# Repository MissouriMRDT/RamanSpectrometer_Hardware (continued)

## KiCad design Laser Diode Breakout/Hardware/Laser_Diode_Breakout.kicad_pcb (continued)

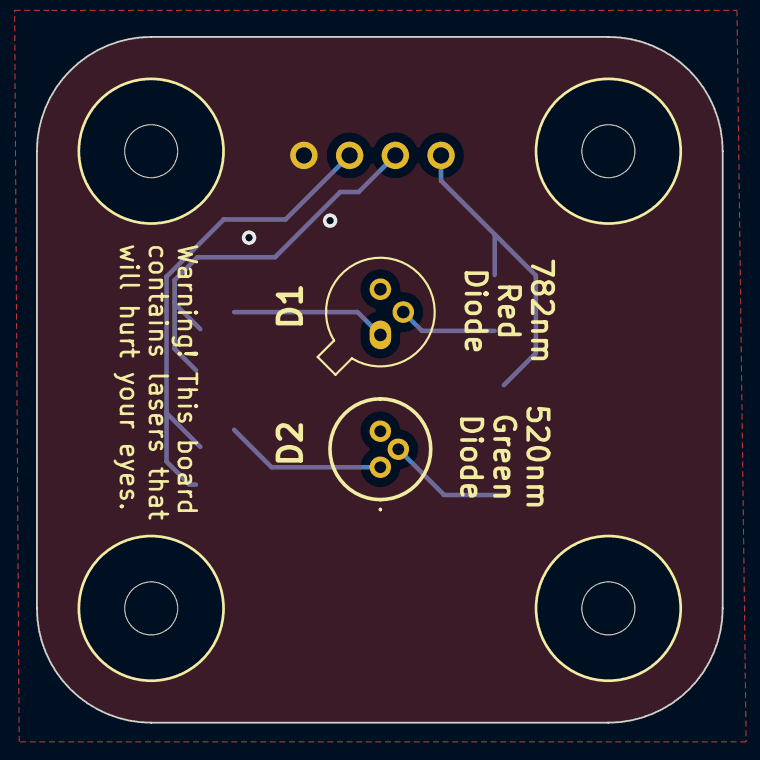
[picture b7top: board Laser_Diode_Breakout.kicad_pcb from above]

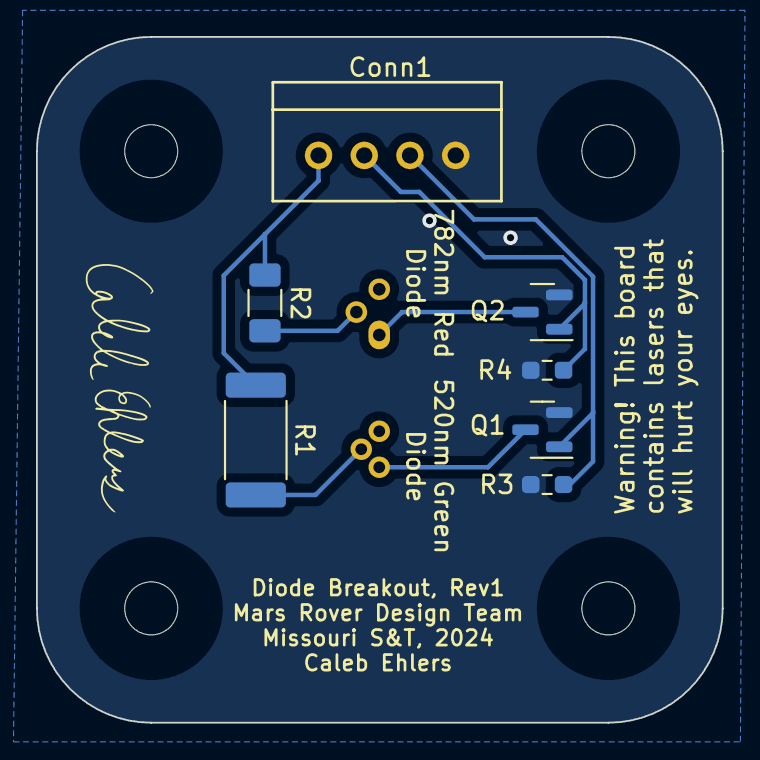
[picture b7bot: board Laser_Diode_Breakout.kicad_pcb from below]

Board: 2 copper layers, 38.1 x 38.1 mm, 13 parts (7 on the bottom side), 8 nets.

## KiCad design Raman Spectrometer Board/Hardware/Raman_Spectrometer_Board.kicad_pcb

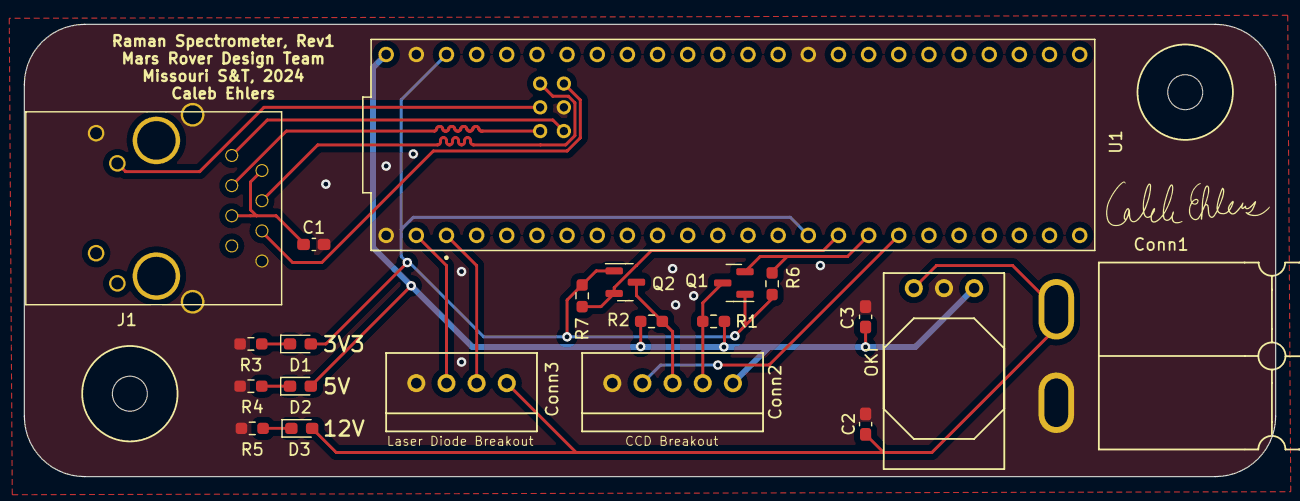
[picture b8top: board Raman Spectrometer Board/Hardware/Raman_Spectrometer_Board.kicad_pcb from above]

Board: 2 copper layers, 105.4 x 38.1 mm, 23 parts (0 on the bottom side), 20 nets.

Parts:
C1: 0.1µF; C_0603_1608Metric_Pad1.08x0.95mm_HandSolder
C2, C3: 10µF; C_0603_1608Metric_Pad1.08x0.95mm_HandSolder
Conn1: AndersonPP; Square_Anderson_2_H_Side_By_Side
Conn2: Molex_SL_05; MOLEX_SL_05_Vertical
Conn3: Molex_SL_04; MOLEX_SL_04_Vertical
D1, D2, D3: Green; LED_0603_1608Metric_Pad1.05x0.95mm_HandSolder
J1: RJ45_LED_Shielded; RJ45_Teensy
Q1, Q2: BSS138; SOT-23
R1, R2, R6, R7: 4.7k; R_0603_1608Metric_Pad0.98x0.95mm_HandSolder
R3: 100; R_0603_1608Metric_Pad0.98x0.95mm_HandSolder
R4: 300; R_0603_1608Metric_Pad0.98x0.95mm_HandSolder
R5: 1k; R_0603_1608Metric_Pad0.98x0.95mm_HandSolder
U1: Teensy4.1_DEV-16771; Teensy_4_1_Ethernet
U2: OKI; OKI_Horizontal
V1, V2: Via; 4_40_Hole

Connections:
+3V3: D1.2 (A), Q1.1 (G), Q2.1 (G), R6.1, R7.1, U1.3.3V_1 (3.3V), U1.3.3V_2 (3.3V)
+5V: C3.1, Conn2.1, D2.2 (A), R1.1, R2.1, U1.VIN, U2.3 (Vo)
+12V: C2.1, Conn1.2 (V+Log), Conn3.1, D3.2 (A), U2.1 (Vi)
CCD_CLK_3V3: Q1.2 (S), R6.2, U1.25 (A11)
CCD_CLK_5V: Conn2.2, Q1.3 (D), R1.2
CCD_ROG_3V3: Q2.2 (S), R7.2, U1.24 (A10)
CCD_ROG_5V: Conn2.3, Q2.3 (D), R2.2
CCD_Vout: Conn2.4, U1.26 (A12)
GND: C1.2, C2.2, C3.2, Conn1.1 (GND), Conn2.5, Conn3.4, J1.8, J1.9, J1.SH, R3.2, R4.2, R5.2, U1.GND1 (GND), U1.GND2 (GND), U1.GND3 (GND), U1.GND5 (GND), U2.2 (GND)
Green_LED: Conn3.3, U1.0 (RX1)
LED: J1.10, U1.LED
unnamed: C1.1, J1.2, J1.5
unnamed: D1.1 (K), R3.1
unnamed: D2.1 (K), R4.1
unnamed: D3.1 (K), R5.1
R+: J1.4, U1.R+
R-: J1.6, U1.R-
Red_LED: Conn3.2, U1.1 (TX1)
T+: J1.1, U1.T+
T-: J1.3, U1.T-

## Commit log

2023-09-09 chore: created CCD Breakout project
2023-09-09 chore: created empty schematics
2023-09-09 feat: add teensy and ethernet
2023-09-09 Adjust file structure
2023-09-11 feat: created ILX511 symbol for CCD Breakout
2023-09-12 //WIP CCD Breakout
2023-09-12 chore: delete duplicate Raman board files
2023-09-15 Finshed CCD breakout
2023-09-24 Made Laser Diode breakout
2023-09-24 added laser breakout to raman board
2023-09-24 finished adding boxes to ramen board
2023-09-24 generated BOM
2023-09-24 I forgot to save everything for the last commit
2023-09-24 fix: switched connectors to Molex
2023-09-25 fix: replaced net labels with text
2023-09-25 misc schematic review changes
2023-09-25 fix: use mosfets to control diodes
2023-09-25 chore: resized Raman Board
2023-09-28 changed AndersonPP to V+ Log
2023-10-02 feat: aligned components for Raman board
2023-10-02 //WIP
2023-10-03 feat: finish Raman board
2023-10-03 fix: changes from malacki
2023-10-13 //WIP working on fixing diodes
    we though one of the diodes required 2V, but that was its reverse voltage. It actually wants 5.9, so we need to change the diode board to account
2023-10-14 fixed resitor values on diode board
2023-10-14 set footprints for most of laser diode breakout
2023-10-14 diode board layout general shape
2023-10-14 finished adding footprints to laser diode breakout
2023-10-14 added footprints to ccd breakout
    added all capacitors
    the only footprint left is the ccd
2023-10-14 closed kicad tabs
2023-10-14 finish diode breakout
2023-10-15 fix: changed ilx511 symbol library path
2023-10-15 created ilx511 footprint
2023-10-15 closed out of kicad tabs
2023-10-15 //WIP start ccd layout
2023-10-15 finish ccd
2023-10-15 added ground plane to diode board
2023-10-15 switched raman board to using vertical molex
2023-10-15 fixed ground plane in diode breakout
2023-10-15 rearrange components on raman board
2023-10-15 added signatures to all boards
2023-10-15 cleaned file structure
2023-10-15 rewired raman board
2023-10-15 clean up 3V3 wires
2023-10-15 removed little random traces
2023-10-15 finished raman board changes
2023-10-15 added label to raman board
2023-10-16 finish diode breakout changes
2023-10-16 adjusted page sizes for all boards
2023-10-16 finish ccd board
2023-10-16 adjust silkscreen on diode board
2023-10-16 adjust silkscreen for raman board
2023-10-16 removed small random traces
2023-10-19 fixed board name silkscreens
2023-10-21 generated step files
2023-10-21 closed kicad
2023-10-21 add 4.7k resistor to mosfets and regenerate BOM
2023-10-21 changes for layout review #2
2023-10-31 generated GERBS
2023-10-31 fix differential pairs and center LEDs on diode board
2023-10-31 regenerate GERBS
2023-11-03 changes from layout review #3
2024-09-26 Reset branch
2024-10-03 Added Diode Control
2024-10-03 Restoring Changes
2024-10-03 fix
    fixed from 2024rev1 push
2024-10-04 Added CCD Breakout
2024-10-04 Mounting Holes / Formatting
2024-10-04 status
2024-10-04 Finished Raman Spectrometer Schematic. Merged Diode Breakout onto the board, but also left a connector in case we use a store-bought diode/external one off the board. Might want to check over the sch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
2024-10-04 Changed Labels
2024-10-05 Gantry and fan connector pins
2024-10-05 Started on BOM. Updated gantry and fan connectors
2024-10-06 Updated BOM a little bit
2024-10-10 Raman Schematic Review
    Made changes to the labels on the gantry connector and teensy.
2024-10-11 Added Mounting Holes
2024-10-11 CCD GND
2024-10-17 updated schematic
2024-10-17 Updated Bill of Materials
2024-10-17 updated BOM again
2024-10-24 footprints
2024-10-24 pcb layout
2024-10-25 PCB Holes
2024-10-26 pcb routing
2024-10-27 PCB rough draft
2024-10-28 PCB revision
2024-10-30 PCB Draft 2
2024-10-30 Started on CCD
2024-10-30 Raman PCB redesign
2024-10-30 Raman PCB revisions
2024-10-31 PCB Raman updates
2024-10-31 PCB Raman again
2024-11-05 PCB Raman 12V Plane
2024-11-05 PCB Raman edit and TOF
2024-11-05 ihateyoujesse
2024-11-07 Raman PCB Additions
2024-11-07 Raman PCB Final
2024-11-07 Updated CCD
2024-11-07 Schematic Changes
2024-11-11 CCD Changes
2024-11-12 Raman PCB board review pt.1
2024-11-12 Raman pt.2
2024-11-12 Raman pt.3 (RIP Comic Sans)
2024-11-13 Raman dimension changes
2024-11-13 Raman dimensions fixed
2024-11-15 More Raman
2024-11-15 Raman Gerbs ... I think
2024-11-15 Fixed thermal reliefs
2024-11-15 CCD Gerbs
2024-11-15 ignore upd; CCD parity; CCD lib
    Added lck file to gitignore
    Fixed parity between CCD schematic and layout
    Made corners of CCD heat sink hole rounded
    Fixed CCD library settings
2024-11-15 fixed ccd breakout for order
2025-03-11 Made a Rev2 branch
2025-03-13 Rev 2 updated
2025-03-17 updated Raman PCB
2025-03-17 Updated CCD SHSW as well as the pin connector between both boards. Still need to adjust an even frame size, adjust length of ethernet cables, generate GERBS, and check all input/output flags, as well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
2025-03-18 Finished Rev2
2025-03-18 Small touchups, Generated Gerbs
2025-03-19 Maaaaaaaan
2025-03-19 Fixed bjt and SL on CCD Breakout
2025-09-12 Added workflow
2025-09-30 Potential Schematic Layout + Basic Power Circuits
2025-09-30 Added Resistors to Power LED's
2025-09-30 Added Teensey
2025-09-30 Added Ethernet
2025-10-01 Added Project for CCD_Breakout
2025-10-01 Added CAN Transceiver
2025-10-02 Moved project files to correct folder
2025-10-02 Added Anderson Connectors
2025-10-02 Servo Connectors
    This definitely, need to be checked.
2025-10-03 Added Diode Connection & Removed Unecessary Pages
    Removed, limit switches and motor controller.
2025-10-05 Possible Laser Diode Connector
2025-10-05 Added Resistor Values to Diode Connector
    I think we need to add some other resistors to this but im not sure. In general not super confident in this.
2025-10-07 Start of FanConnector
2025-10-08 CCD start
2025-10-08 fanConnector
2025-10-08 CCD Fixed
2025-10-08 Omp amp added
2025-10-08 CCD Connector
2025-10-08 CCD Reorganization
2025-10-08 Added Missing Resistors to CCD
2025-10-08 ACD Symbol Added (no functionality)
2025-10-08 ADC Changes + Delete Fan Connector
2025-10-08 fan connectors
2025-10-08 TOF sensor
2025-10-08 connect
2025-10-09 Adding Decouplers
2025-10-09 Honestly a bunch of rapid changes
    CCD ADC
2025-10-10 Removed Unnecessary Filtering Capacitors
2025-10-10 tof BETTER GO THROUGH
2025-10-10 CCD clock without teensy connect
2025-10-10 known teensey connectors connected
2025-10-10 Possible Buffer Design
2025-10-10 Connecting CCD to Teensy
2025-10-10 Added filtering capacitors on ADC
2025-10-15 ADC 1.8 Pin
2025-10-15 Gantry Motor Andersons Added
2025-10-16 OpAmp IC
2025-10-16 L gantry
2025-10-16 ST and EOS Pin Connections
2025-10-16 Labels, and datasheets
2025-10-16 Labels change for clock pins
2025-10-21 Added footprints to main board
2025-10-21 Fixed CAN Footprint
2025-10-21 CCD Footprints
    ADC and CCD footprints needed
2025-10-21 Fixed CCD Footprints
2025-10-21 Added Footprints to main board layout
2025-10-22 loose voltage connected
2025-10-22 tof voltages connected
2025-10-22 Revert "tof voltages connected"
    This reverts commit cb392bf1d60e7f863b02c943ae62205c2a2451bd.
2025-10-22 R9 fixed
2025-10-22 octal buffer wires fixed
2025-10-23 Placed laser driver connector
2025-10-23 Page Consolidation
2025-10-23 Fixed CAN page
2025-10-23 Resistors and Indicator LED to Diode Driver
2025-10-23 High Side Fan Connector
2025-10-23 Added filtering capacitor to buffer
2025-10-23 Added Graphical Indication of the Op Amps
2025-10-23 Added 3.3v to the CCD
2025-10-23 Added 3.3v to ADC
2025-10-23 Added differential opamp circuit and 0.6V shottky voltage reference
2025-10-24 OP amp filtered
2025-10-24 zener diode
2025-10-24 Diode Connector
2025-10-24 Fixed Voltage
2025-10-26 Draft layout design
2025-10-26 Power Layout
2025-10-26 Ethernet Connector Layout
2025-10-26 Servo Molex Connectors
2025-10-26 Laser Diode Connector Layout
2025-10-26 Fan Driver Layout
2025-10-26 TOF and CCD Connector Layout
2025-10-26 CAM1 Connector
2025-10-28 CAN Layout
2025-10-30 Fix Layout Issues
2025-10-31 Fixed laser driver power switching circuit
2025-10-31 Initial layout
2025-11-01 CCD Positional Layout
2025-11-01 CCD Layout Traces
2025-11-01 Added Reverse Voltage Protection
2025-11-01 Fix Diode Connector
2025-11-01 Fix Traces
2025-11-01 Resized Raman Layout
2025-11-01 Added missing traces
2025-11-01 Push
2025-11-06 typos
2025-11-06 shunt regulator fixed from .6 to 1 V
2025-11-06 CCD update
2025-11-06 Fix Resistor Footprints
2025-11-07 CCD Push
2025-11-08 Trace Width Fix
2025-11-09 Redo Differential Pairs
2025-11-09 Raman Fixes
2025-11-09 R5 resistor moved
    moved R5 so that it is no longer too close to the edge of the board
2025-11-10 Resistor footprints
    R12-15 have been changed to 0603 hand soder footprints.
2025-11-10 Resistor changes (schematic)
    Forgot to add this with the other push for resistor footprints
2025-11-11 Lib changes
2025-11-11 New CCD Design
2025-11-11 New Power Connectors
2025-11-11 Add Motor Buttons
2025-11-12 labelling connectors
2025-11-12 limit switch connectors
2025-11-12 sheet pins
2025-11-12 CRD Issues
2025-11-12 Fix CDR
2025-11-12 no connects
2025-11-12 labeling
2025-11-14 layout labelling
2025-11-14 Fixed switch connections
2025-11-14 PCB final design? maybe
2025-11-14 signature
2025-11-15 CCD Check
2025-11-16 CCD Silkscreens
2025-11-16 Signature
    Added Signature
2025-11-17 Fix a couple missed connections and via stitching
2025-11-17 Fix kicad action paths
2025-11-17 Fix a couple of traces and do final check
2025-11-18 Add test points
2025-11-18 Fix silkscreens
2025-12-10 Add 3D models
2026-02-11 Board redesign for laser engraving
2026-03-11 Rev2 Push
2026-03-11 Rev 2 Layout
2026-03-12 Rev2 alt
2026-03-13 Moved CCD files out of copied folders
2026-03-13 Deleted auto save
2026-03-13 Added laser driver sheet
2026-03-14 Raman Board Rev 2 start
2026-03-15 Rev2 Layout
2026-03-16 Added some laser driver footprints and 3d models
2026-03-16 Ground vias
2026-03-16 CMOS vias
2026-03-16 CMOS vias alt
2026-03-16 Validated all footprints and models
2026-03-16 Began re-laying out laser driver section
2026-03-16 Finished laser diode layout
2026-03-16 Minor routing changes
2026-03-16 Added polygons to buck caps
2026-03-16 Silkscreen change
2026-03-17 Silkscreen fix
2026-03-17 Raman CAN Move
2026-03-17 Can move
2026-03-17 Switch to 12v plane
2026-03-17 Silkscreen fixes
2026-03-17 Silkscreen Update
2026-03-17 DRC Fix
2026-03-18 3d Models added
2026-03-18 3d Models
2026-03-19 Fix DRC issues
2026-03-19 SCH fixes
2026-03-19 Laser switch
2026-03-19 Rev2 Fixes
2026-03-21 laser driver xshut pin
2026-03-21 Fixed SHDN
2026-03-21 Miscellaneous schematic fixes
2026-03-21 Dimensions
2026-03-21 Laser driver capacitor
2026-03-21 Deleting
2026-03-21 Fix merge issues
2026-03-21 Clean up file structure
2026-03-21 Fix file structure
2026-03-21 Finalize board design
2026-03-21 Added 1uF capacitor to CMOS
2026-03-22 Fixed CMOS capacitor silkscreen
2026-03-22 Fixed Commit schematic
2026-03-23 Post review laser driver edits
2026-03-23 CCD Labels
2026-03-23 fix 5v trace
2026-03-23 build ground planes
2026-03-23 Final design files as ordered
2026-03-23 Final CMOS breakout design files as ordered
